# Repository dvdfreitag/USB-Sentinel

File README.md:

USB-Sentinel
============

This is the main repository for the USB Sentinel project. It was created in response to the threat of hacked USB devices. More information can be found [here](https://www.youtube.com/watch?v=nuruzFqMgIw "Youtube: BadUSB - On Accessories that Turn Evil by Karsten Nohl + Jakob Lell").

Powered by [LUFA](http://www.fourwalledcubicle.com/LUFA.php) by Dean Camera

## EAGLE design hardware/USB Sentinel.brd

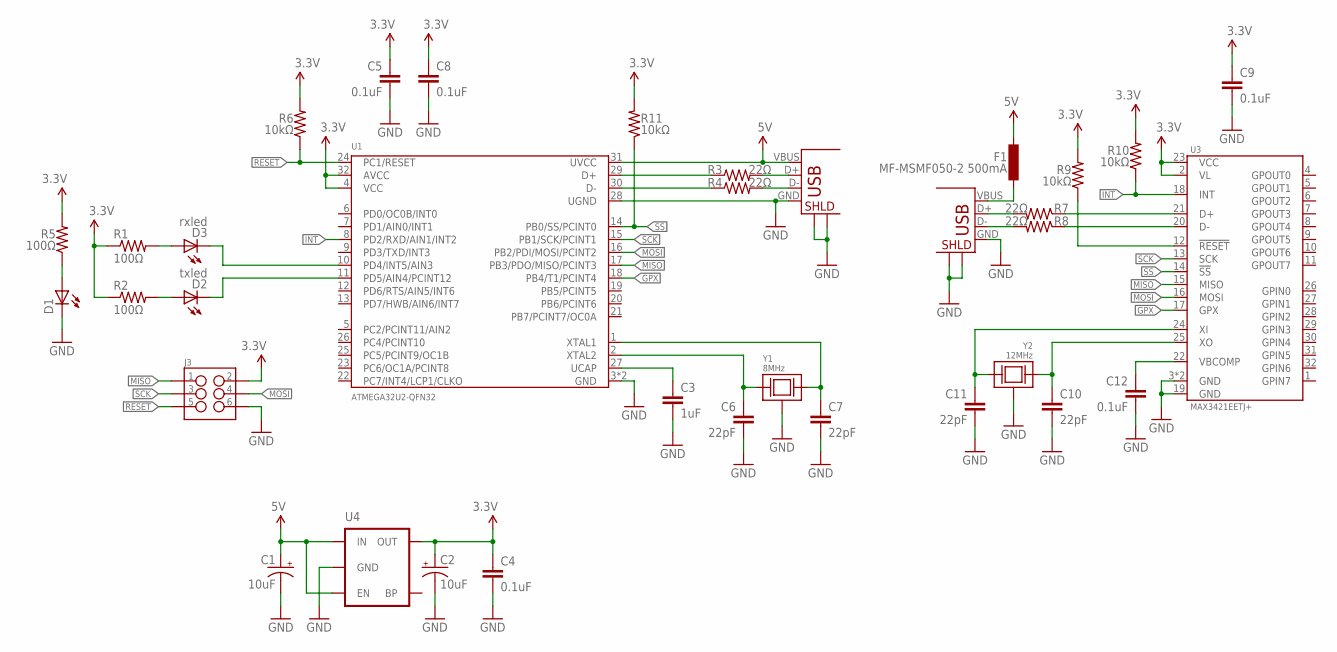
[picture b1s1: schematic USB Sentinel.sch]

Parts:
C1, C2: 10uF; 0805-CAP_POL
C3: 1uF; 0402-CAP
C4, C5, C8, C9, C12: 0.1uF; 0402-CAP
C6, C7, C10, C11: 22pF; 0402-CAP
D1: LED0603; LED-0603
D2: txled; LED-0603
D3: rxled; LED-0603
F1: MF-MSMF050-2 500mA; L1812
J1: USB+SHIELD-MICROB; USB-MICROB
J2: USB+SHIELD-A-S; USB-A-S
J3: M03X2-50MIL
R1, R2, R5: 100Ω; 0402-RES
R3, R4, R7, R8: 22Ω; 0402-RES
R6, R9, R10, R11: 10kΩ; 0402-RES
U1: ATMEGA32U2-QFN32; QFN-32
U3: MAX3421EETJ+; QFN-32
U4: V_REG_LDOSMD; SOT23-5
Y1: 8MHz; CRYSTAL-5X3.2
Y2: 12MHz; ECX-32

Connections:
3.3V: C2.A (+), C4.1, C5.1, C8.1, C9.1, J3.2, R1.1, R2.1, R5.2, R6.2, R9.2, R10.2, R11.2, U1.4 (VCC), U1.32 (AVCC), U3.2 (VL), U3.23 (VCC), U4.5 (OUT)
5V: C1.A (+), F1.1, J1.VBUS, U1.31 (UVCC), U4.1 (IN), U4.3 (EN)
GND: C1.C (-), C2.C (-), C3.2, C4.2, C5.2, C6.2, C7.2, C8.2, C9.2, C10.2, C11.2, C12.2, D1.C, J1.GND, J1.MT1, J1.MT2, J1.P$1, J1.P$2, J2.GND, J2.P$5, J2.P$6, J3.6, U1.3 (GND), U1.28 (UGND), U1.EP (GND), U3.3 (GND), U3.19 (GND), U3.EP (GND), U4.2 (GND), Y1.2 (GND), Y1.4 (GND), Y2.2 (GND), Y2.4 (GND)
GPX: U1.18 (PB4/T1/PCINT4), U3.17 (GPX)
INT: R10.1, U1.8 (PD2/RXD/AIN1/INT2), U3.18 (INT)
MISO: J3.1, U1.17 (PB3/PDO/MISO/PCINT3), U3.15 (MISO)
MOSI: J3.4, U1.16 (PB2/PDI/MOSI/PCINT2), U3.16 (MOSI)
unnamed: C3.1, U1.27 (UCAP)
unnamed: D3.C, U1.10 (PD4/INT5/AIN3)
unnamed: D2.C, U1.11 (PD5/AIN4/PCINT12)
unnamed: D3.A, R1.2
unnamed: D2.A, R2.2
unnamed: R3.1, U1.29 (D+)
unnamed: R4.1, U1.30 (D-)
unnamed: J1.D+, R3.2
unnamed: J1.D-, R4.2
unnamed: D1.A, R5.1
unnamed: F1.2, J2.VBUS
unnamed: J2.D+, R7.2
unnamed: J2.D-, R8.2
unnamed: R7.1, U3.21 (D+)
unnamed: R8.1, U3.20 (D-)
unnamed: C10.1, U3.25 (XO), Y2.1
unnamed: C11.1, U3.24 (XI), Y2.3
unnamed: C12.1, U3.22 (VBCOMP)
unnamed: R9.1, U3.12 (!RESET)
unnamed: C6.1, U1.2 (XTAL2), Y1.1
unnamed: C7.1, U1.1 (XTAL1), Y1.3
RESET: J3.5, R6.1, U1.24 (PC1/RESET)
SCK: J3.3, U1.15 (PB1/SCK/PCINT1), U3.13 (SCK)
SS: R11.1, U1.14 (PB0/SS/PCINT0), U3.14 (!SS)

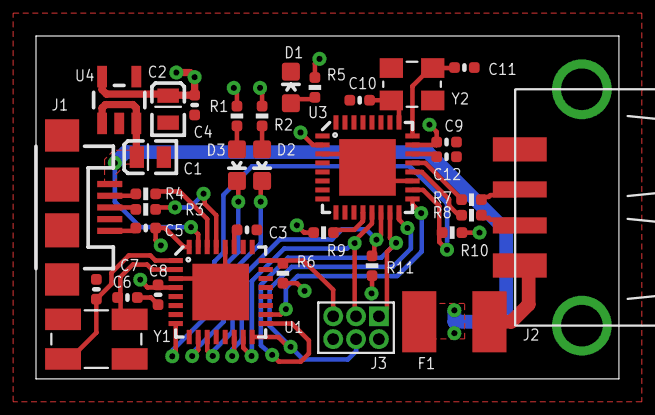
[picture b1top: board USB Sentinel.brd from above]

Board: 2 copper layers, 32.4 x 19.1 mm, 35 parts (0 on the bottom side), 31 nets.

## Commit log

2014-09-04 :lollipop: Added .gitattributes & .gitignore files
2014-09-05 Added Hardware Files
    Added Cadsoft Eagle PCB/Schematic files as well as the gerber files for
    the PCB.
2014-09-05 Added license file
2014-09-05 Added Atmel Studio to gitignore
2014-09-05 Added Atmel Studio to gitattributes
2014-09-05 Added Visual Studio gitignore
2014-09-05 Added Schematic PDF
2014-09-05 Added Caterina bootloader
2014-09-05 Update gitignore
2014-09-05 Updated PCB
    Changed a few things on the PCB to help with production.
2014-09-06 Update build script
2014-09-13 Update gitignore
    Added Atmel Studio gitignores
2014-09-13 Updated bootloader
    Changed caterina bootloaders and added atmel studio solution
2014-09-13 Removed old bootloader

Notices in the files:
parts and their libraries:
SparkFun-Passives: Licensing: CC v3.0 Share-Alike You are welcome to use this library for commercial purposes.
SparkFun-Connectors: Licensing: Creative Commons ShareAlike 4.0 International - https://creativecommons.org/licenses/by-sa/4.0
